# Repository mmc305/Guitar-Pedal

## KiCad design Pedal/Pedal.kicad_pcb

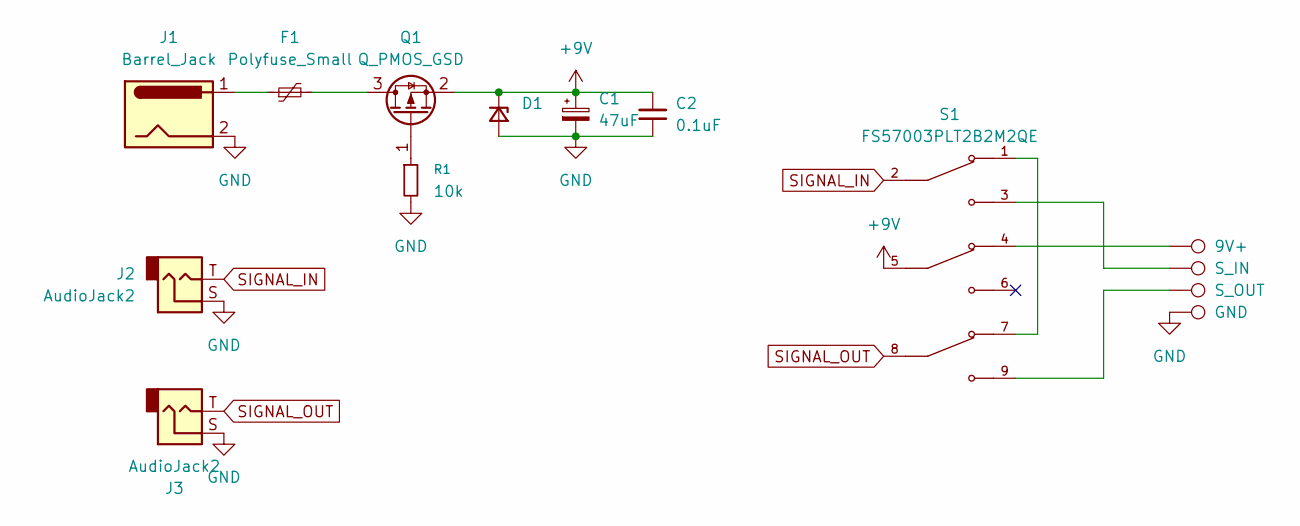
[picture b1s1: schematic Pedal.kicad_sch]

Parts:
C1: 47uF; CP_Radial_D6.3mm_P2.50mm
C2: 0.1uF; C_0603_1608Metric
D1: D_Zener_Small; D_SMA
F1: Polyfuse_Small; Fuse_2920_7451Metric
J1: Barrel_Jack; BarrelJack_GCT_DCJ200-10-A_Horizontal
J2, J3: AudioJack2; Jack_6.35mm_Neutrik_NMJ6HFD2_Horizontal
Q1: Q_PMOS_GSD; TSOT-23
R1: 10k; C_0603_1608Metric
S1: FS57003PLT2B2M2QE; SW_FS57003PLT2B2M2QE; PARTREV 4.2.2018
TP1: 9V+; TestPoint_Keystone_5019_Miniature
TP2: S_IN; TestPoint_Keystone_5019_Miniature
TP3: S_OUT; TestPoint_Keystone_5019_Miniature
TP4: GND; TestPoint_Keystone_5019_Miniature

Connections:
+9V: C1.1, C2.1, D1.1 (K), Q1.2 (S), S1.5
GND: C1.2, C2.2, D1.2 (A), J1.2, J2.S, J3.S, R1.2, TP4.1 (1_1)
unnamed: F1.1, J1.1
unnamed: F1.2, Q1.3 (D)
unnamed: Q1.1 (G), R1.1
unnamed: S1.1, S1.7
unnamed: S1.3, TP2.1 (1_1)
unnamed: S1.4, TP1.1 (1_1)
unnamed: S1.9, TP3.1 (1_1)
SIGNAL_IN: J2.T, S1.2
SIGNAL_OUT: J3.T, S1.8

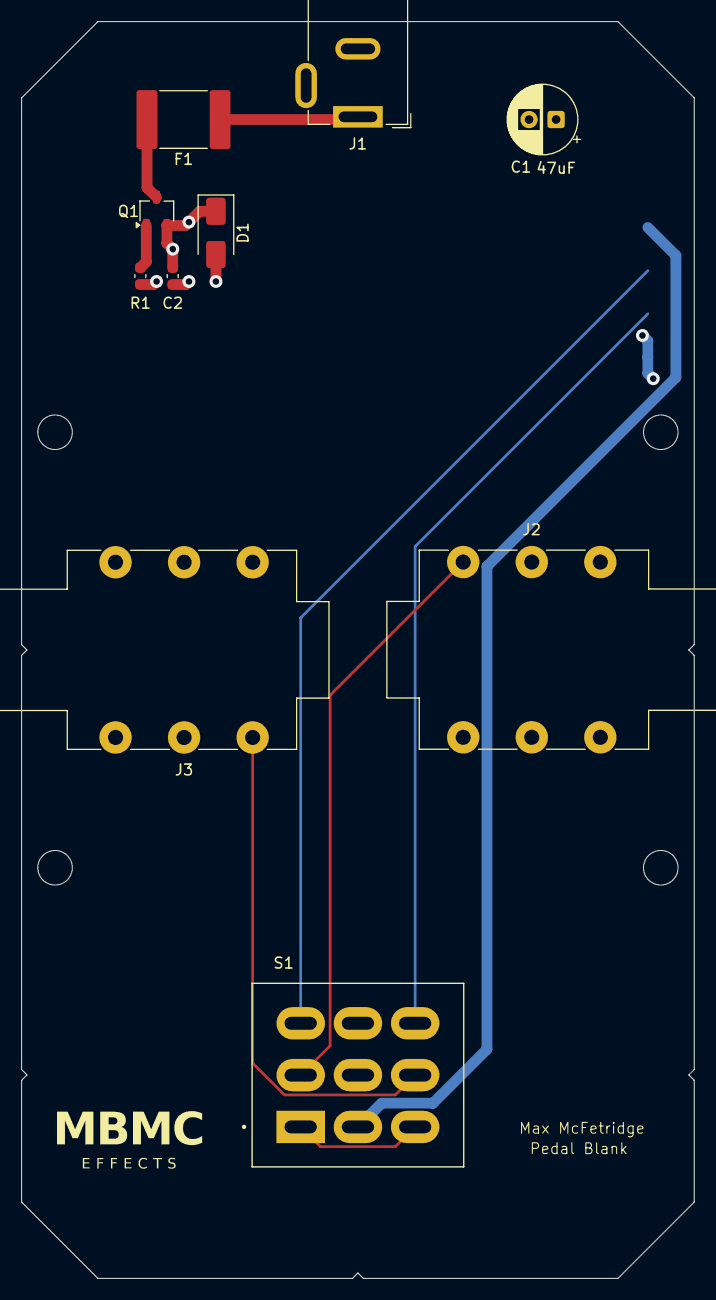
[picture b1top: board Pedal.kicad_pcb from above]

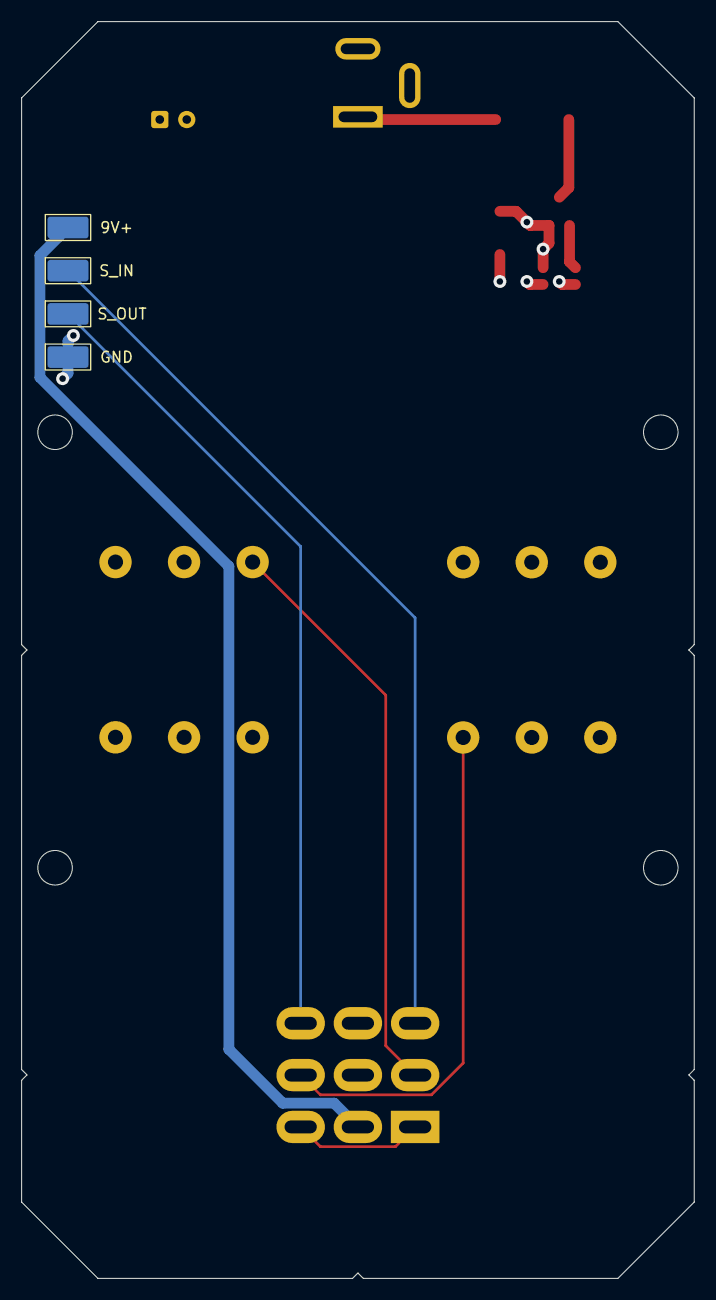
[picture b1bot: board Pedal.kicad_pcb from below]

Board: 4 copper layers, 62.3 x 116.4 mm, 14 parts (4 on the bottom side), 11 nets.

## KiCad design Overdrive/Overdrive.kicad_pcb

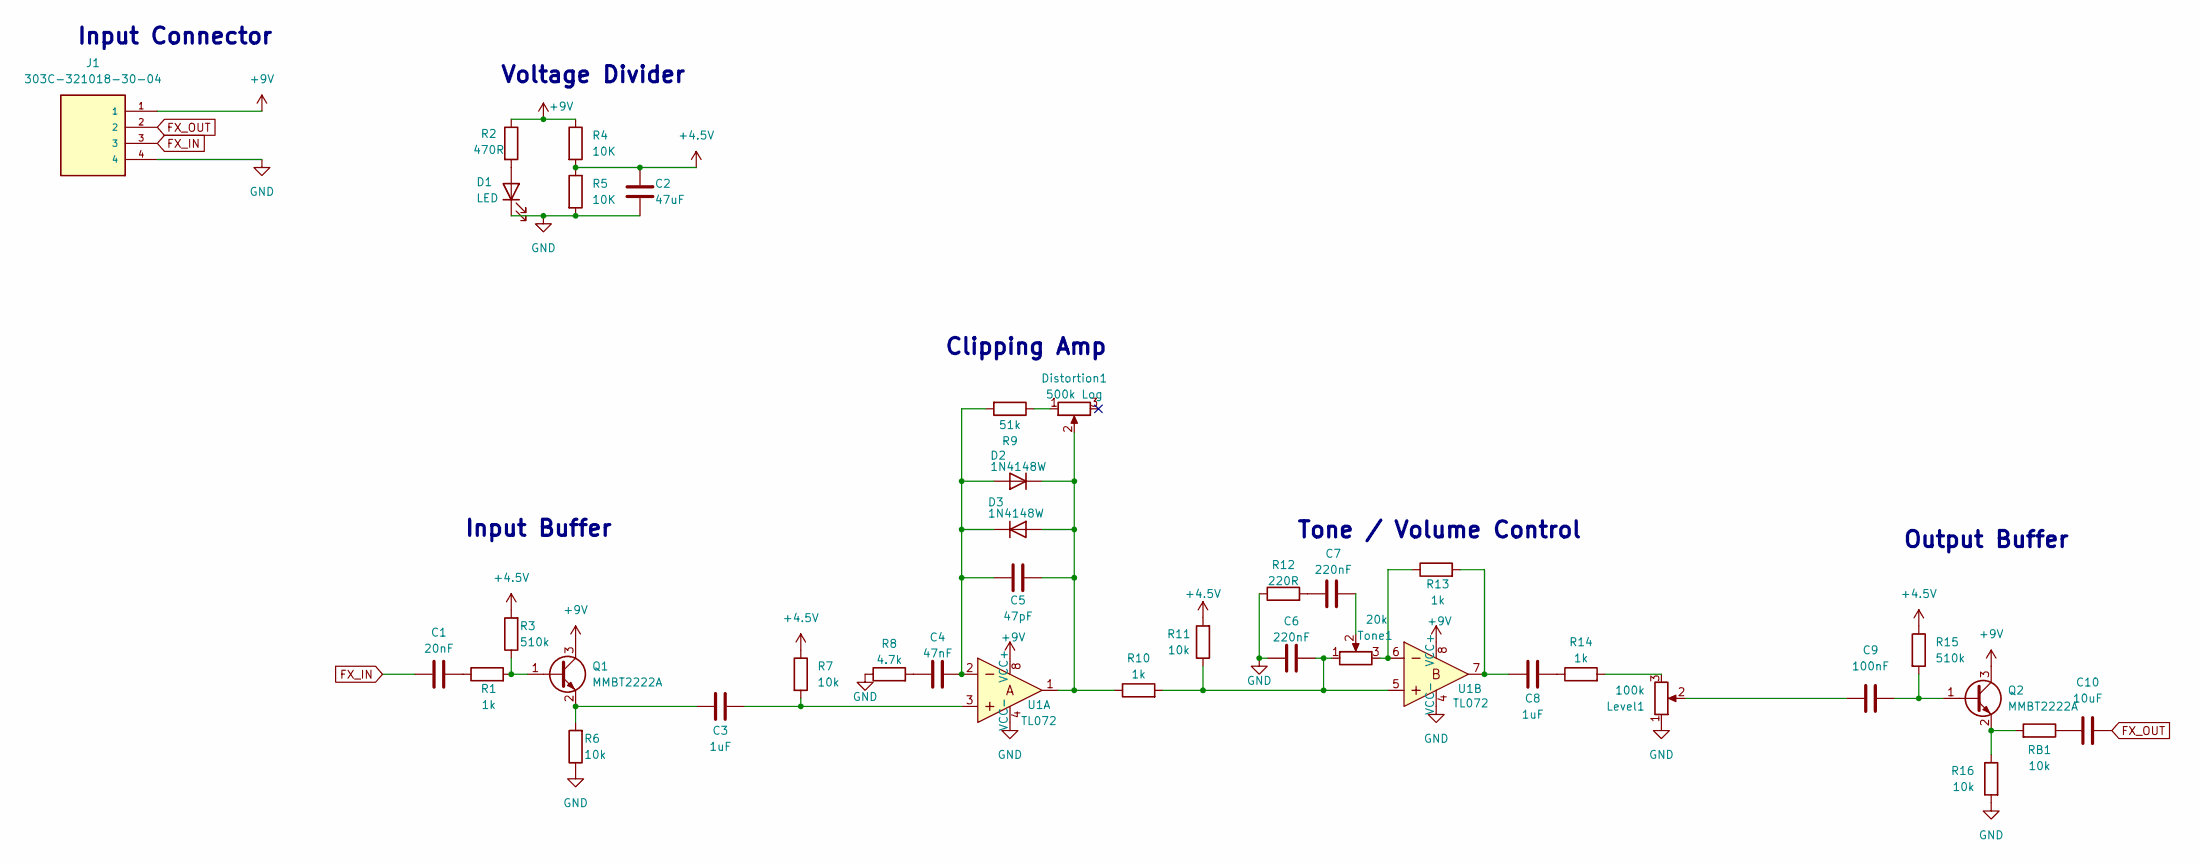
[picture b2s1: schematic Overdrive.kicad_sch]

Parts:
C1: 20nF; C_0603_1608Metric
C2: 47uF; C_0603_1608Metric
C3, C8: 1uF; C_0603_1608Metric
C4: 47nF; C_0603_1608Metric
C5: 47pF; C_0603_1608Metric
C6, C7: 220nF; C_0603_1608Metric
C9: 100nF; C_0603_1608Metric
C10: 10uF; C_0603_1608Metric
D1: LED; LED_D3.0mm_Clear
D2, D3: 1N4148W; D_SOD-123
Distortion1: 500k Log; POT_PTV09A-4020F_BRN
J1: 303C-321018-30-04; ATTEND_303C-321018-30-04; PARTREV 3; DigiKey_Part_Number 4827-303C-321018-30-04-ND
Level1: 100k; POT_PTV09A-4020F_BRN
Q1, Q2: MMBT2222A; SOT-23
R1, R10, R13, R14: 1k; R_0603_1608Metric
R2: 470R; R_0603_1608Metric
R3, R15: 510k; R_0603_1608Metric
R4, R5: 10K; R_0603_1608Metric
R6, R7, R11, R16: 10k; R_0603_1608Metric
R8: 4.7k; R_0603_1608Metric
R9: 51k; R_0603_1608Metric
R12: 220R; R_0603_1608Metric
RB1: 10k; R_0603_1608Metric
Tone1: 20k; POT_PTV09A-4020F_BRN
U1: TL072; SOIC-8_3.9x4.9mm_P1.27mm; MPN TL072CP; Digi-Key_PN 296-1775-5-ND

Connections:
+4.5V: C2.1, R3.2, R4.2, R5.1, R7.1, R11.2, R15.1
+9V: J1.1, Q1.3 (C), Q2.3 (C), R2.1, R4.1, U1.8 (VCC+)
FX_IN: C1.1, J1.3
FX_OUT: C10.2, J1.2
GND: C2.2, C6.1, D1.1 (K), J1.4, Level1.1, R5.2, R6.1, R8.1, R12.1, R16.2, U1.4 (VCC-)
unnamed: C1.2, R1.1
unnamed: C3.2, R7.2, U1.3
unnamed: C4.1, R8.2
unnamed: C6.2, R10.2, R11.1, Tone1.1, U1.5
unnamed: C7.1, Tone1.2
unnamed: C7.2, R12.2
unnamed: C8.1, R13.2, U1.7
unnamed: C8.2, R14.1
unnamed: C9.1, Level1.2
unnamed: C10.1, RB1.1
unnamed: D1.2 (A), R2.2
unnamed: C4.2, C5.1, D2.2 (A), D3.1 (K), R9.2, U1.2
unnamed: C5.2, D2.1 (K), D3.2 (A), Distortion1.2, R10.1, U1.1
unnamed: Distortion1.1, R9.1
unnamed: Level1.3, R14.2
unnamed: Q1.1 (B), R1.2, R3.1
unnamed: C3.1, Q1.2 (E), R6.2
unnamed: C9.2, Q2.1 (B), R15.2
unnamed: Q2.2 (E), R16.1, RB1.2
unnamed: R13.1, Tone1.3, U1.6

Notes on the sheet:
Input Buffer
Clipping Amp
Voltage Divider
Tone / Volume Control
Output Buffer
Input Connector

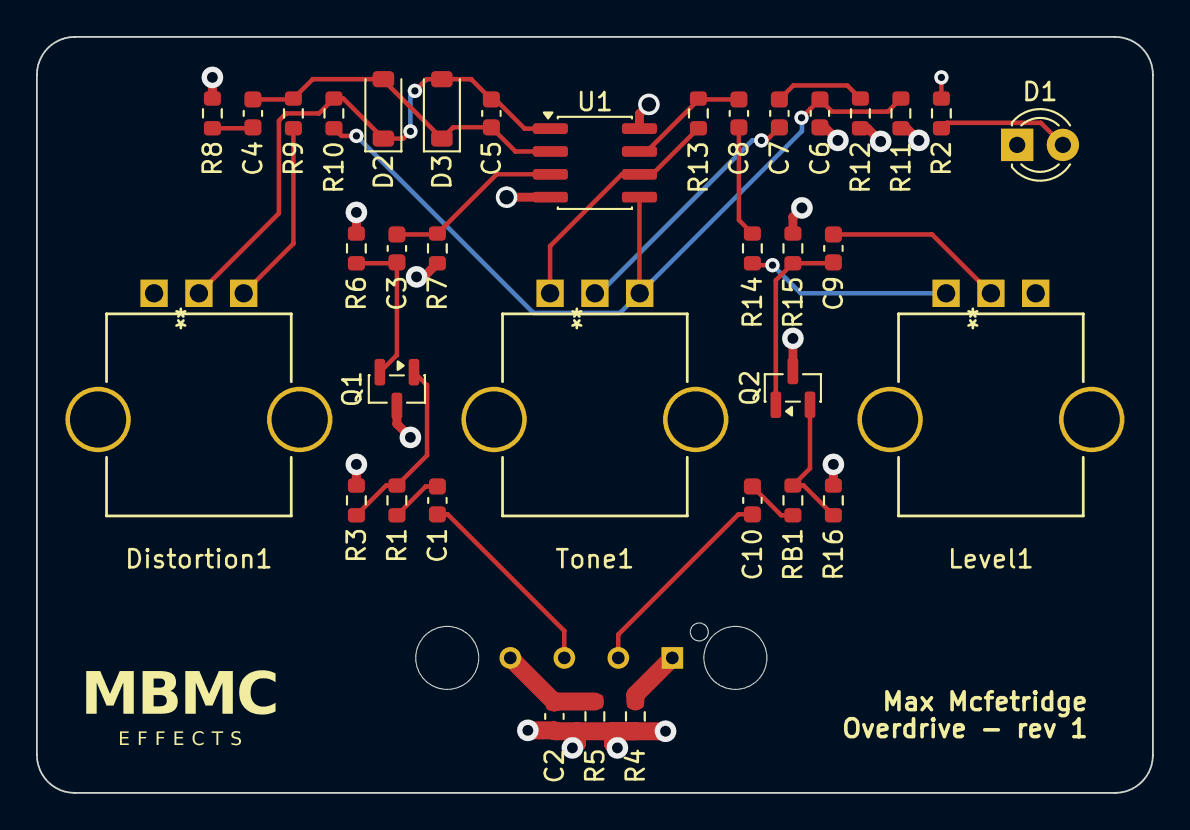
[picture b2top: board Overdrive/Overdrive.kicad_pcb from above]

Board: 4 copper layers, 62.0 x 42.0 mm, 37 parts (1 on the bottom side), 25 nets.

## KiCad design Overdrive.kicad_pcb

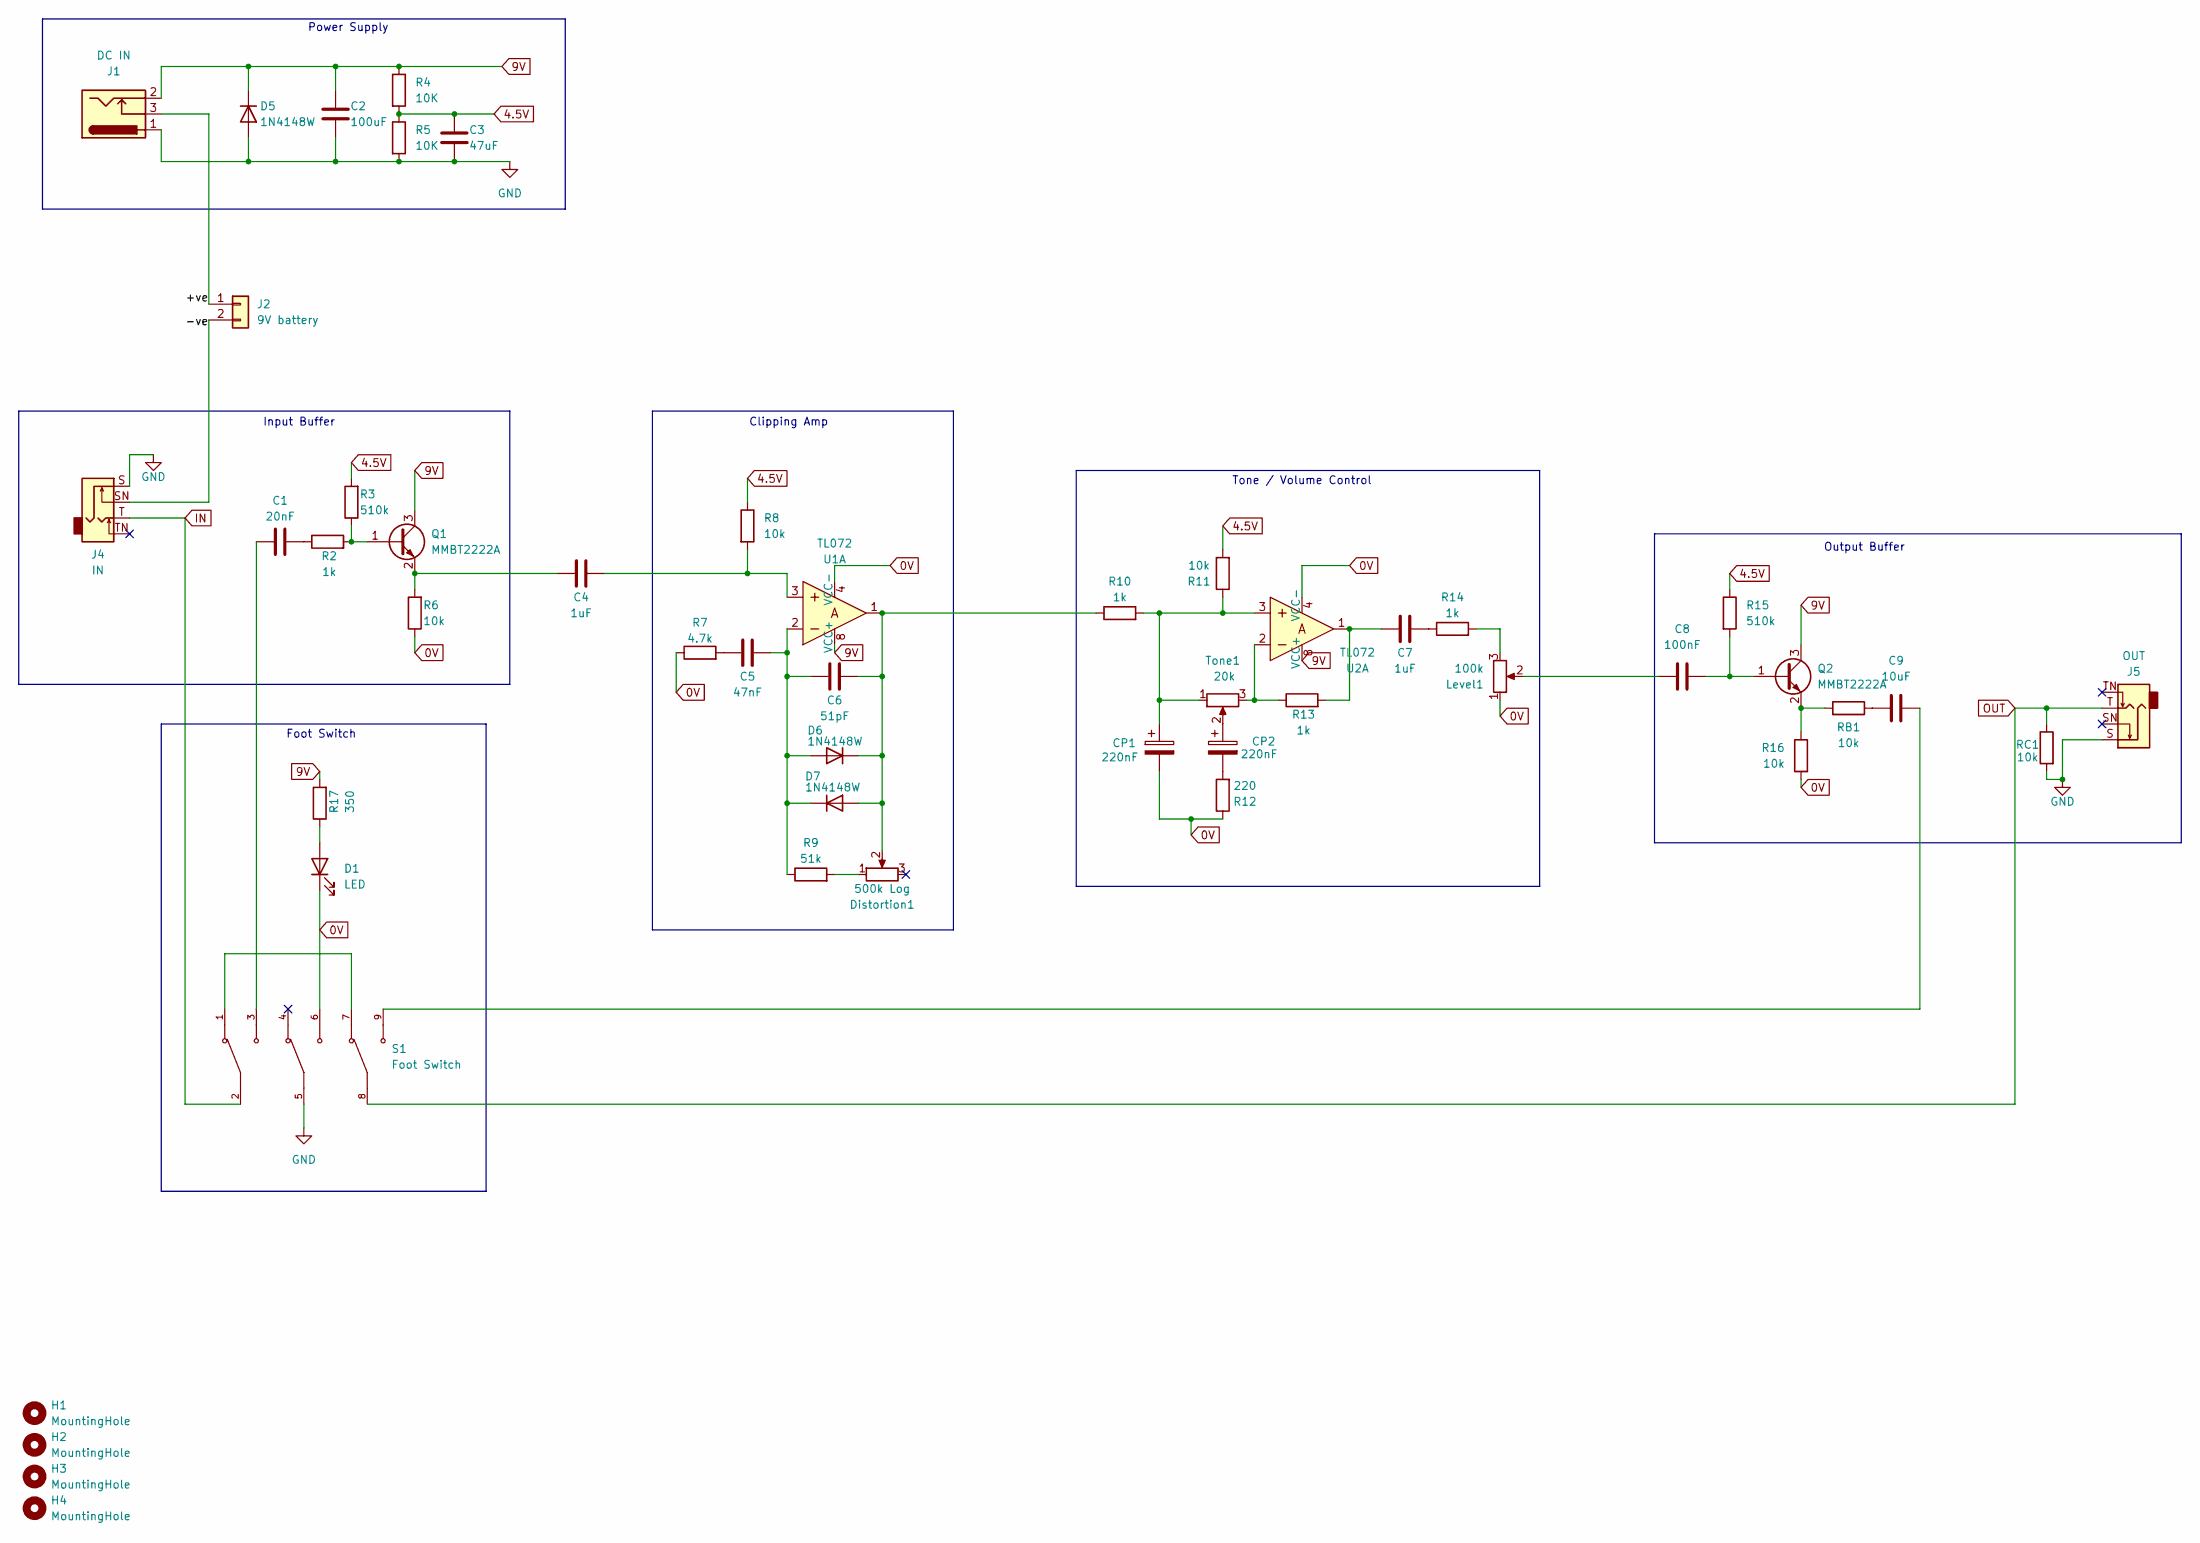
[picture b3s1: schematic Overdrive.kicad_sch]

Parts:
C1: 20nF; C_0603_1608Metric
C2: 100uF; C_1206_3216Metric
C3: 47uF; C_0805_2012Metric
C4, C7: 1uF; C_0603_1608Metric
C5: 47nF; C_0603_1608Metric
C6: 51pF; C_0603_1608Metric
C8: 100nF; C_0603_1608Metric
C9: 10uF; C_0603_1608Metric
CP1, CP2: 220nF; C_0603_1608Metric
D1: LED; LED_D3.0mm_Clear
D5, D6, D7: 1N4148W; D_SOD-123
Distortion1: 500k Log; Potentiometer_RK097_Single_Vertical
H1, H2, H3, H4: MountingHole; MountingHole_3.2mm_M3_Pad_Via
J1: DC IN; BarrelJack_GCT_DCJ200-10-A_Horizontal
J2: 9V battery; PinSocket_1x02_P2.00mm_Vertical
J4: IN; Jack_6.35mm_Neutrik_NMJ6HFD2_Horizontal
J5: OUT; Jack_6.35mm_Neutrik_NMJ6HFD2_Horizontal
Level1: 100k; Potentiometer_RK097_Single_Vertical
Q1, Q2: MMBT2222A; SOT-23
R2, R10, R13, R14: 1k; R_0603_1608Metric
R3, R15: 510k; R_0603_1608Metric
R4, R5: 10K; R_0603_1608Metric
R6, R8, R11, R16: 10k; R_0603_1608Metric
R7: 4.7k; R_0603_1608Metric
R9: 51k; R_0603_1608Metric
R12: 220; R_0603_1608Metric
R17: 350; R_0603_1608Metric
RB1: 10k; R_0603_1608Metric
RC1: 10k; R_0603_1608Metric
S1: Foot Switch; 3PDT Foot Switch
Tone1: 20k; Potentiometer_RK097_Single_Vertical
U1, U2: TL072; SOIC-8_3.9x4.9mm_P1.27mm; MPN TL072CP; Digi-Key_PN 296-1775-5-ND

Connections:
0V: CP1.2, D1.1 (K), Level1.1, R6.1, R7.1, R12.1, R16.2, S1.6, U1.4 (VCC-), U2.4 (VCC-)
4.5V: C3.1, R3.2, R4.2, R5.1, R8.1, R11.2, R15.1
9V: C2.1, D5.1 (K), J1.2, Q1.3 (C), Q2.3 (C), R4.1, R17.2, U1.8 (VCC+), U2.8 (VCC+)
/+ve: J1.3, J2.1
/-ve: J2.2, J4.SN
GND: C2.2, C3.2, D5.2 (A), J1.1, J4.S, J5.S, R5.2, RC1.2, S1.5
IN: J4.T, S1.2
unnamed: C1.1, S1.3
unnamed: C1.2, R2.1
unnamed: C4.2, R8.2, U1.3
unnamed: C5.1, R7.2
unnamed: C7.1, R13.2, U2.1
unnamed: C7.2, R14.1
unnamed: C8.1, Level1.2
unnamed: C9.1, RB1.1
unnamed: C9.2, S1.9
unnamed: CP1.1, R10.2, R11.1, Tone1.1, U2.3
unnamed: CP2.1, Tone1.2
unnamed: CP2.2, R12.2
unnamed: D1.2 (A), R17.1
unnamed: C5.2, C6.1, D6.2 (A), D7.1 (K), R9.1, U1.2
unnamed: C6.2, D6.1 (K), D7.2 (A), Distortion1.2, R10.1, U1.1
unnamed: Distortion1.1, R9.2
unnamed: Level1.3, R14.2
unnamed: Q1.1 (B), R2.2, R3.1
unnamed: C4.1, Q1.2 (E), R6.2
unnamed: C8.2, Q2.1 (B), R15.2
unnamed: Q2.2 (E), R16.1, RB1.2
unnamed: R13.1, Tone1.3, U2.2
unnamed: S1.1, S1.7
OUT: J5.T, RC1.1, S1.8

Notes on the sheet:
Clipping Amp
Output Buffer
Tone / Volume Control
Input Buffer
Foot Switch
Power Supply

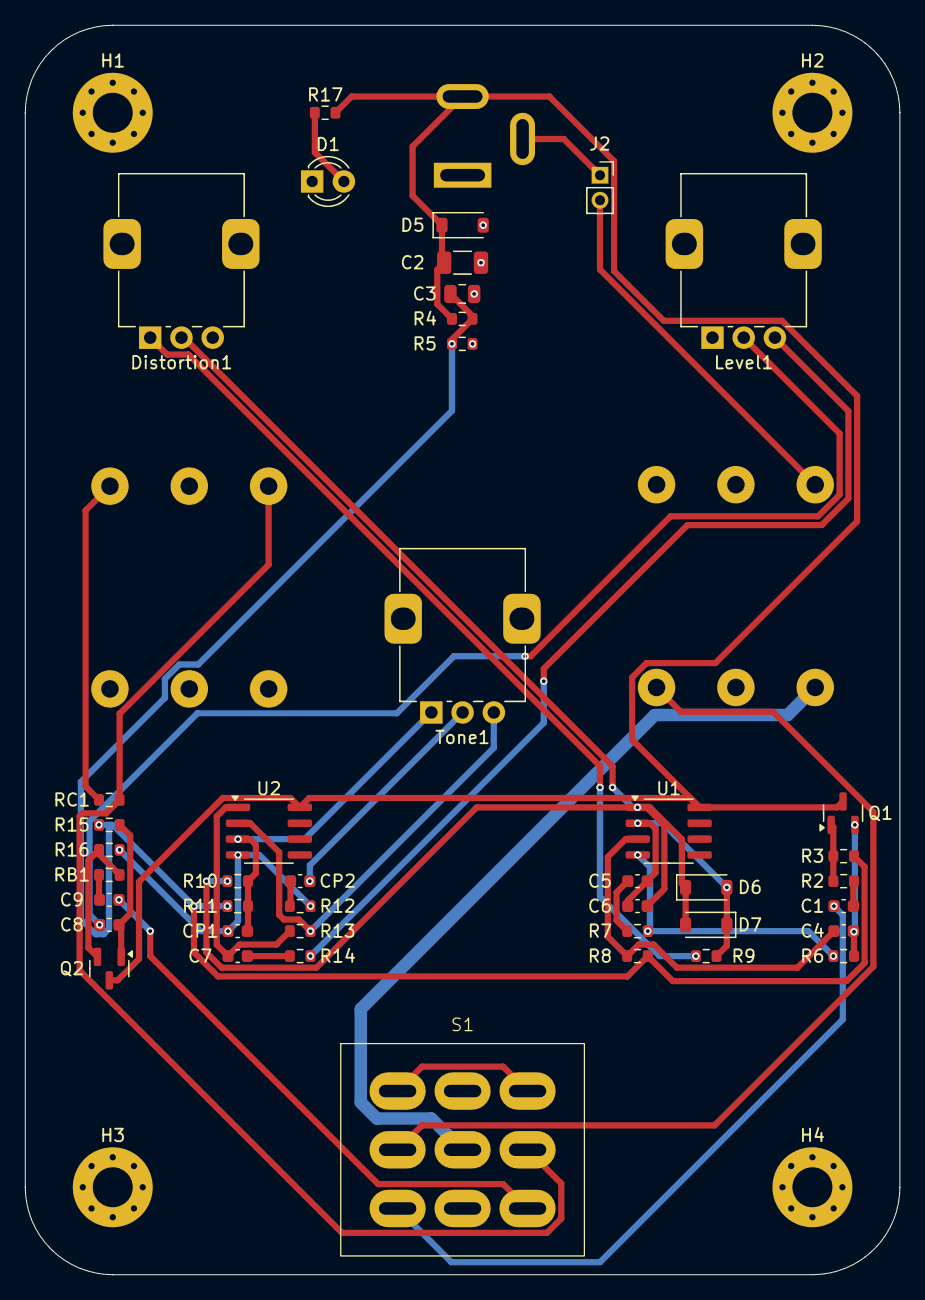
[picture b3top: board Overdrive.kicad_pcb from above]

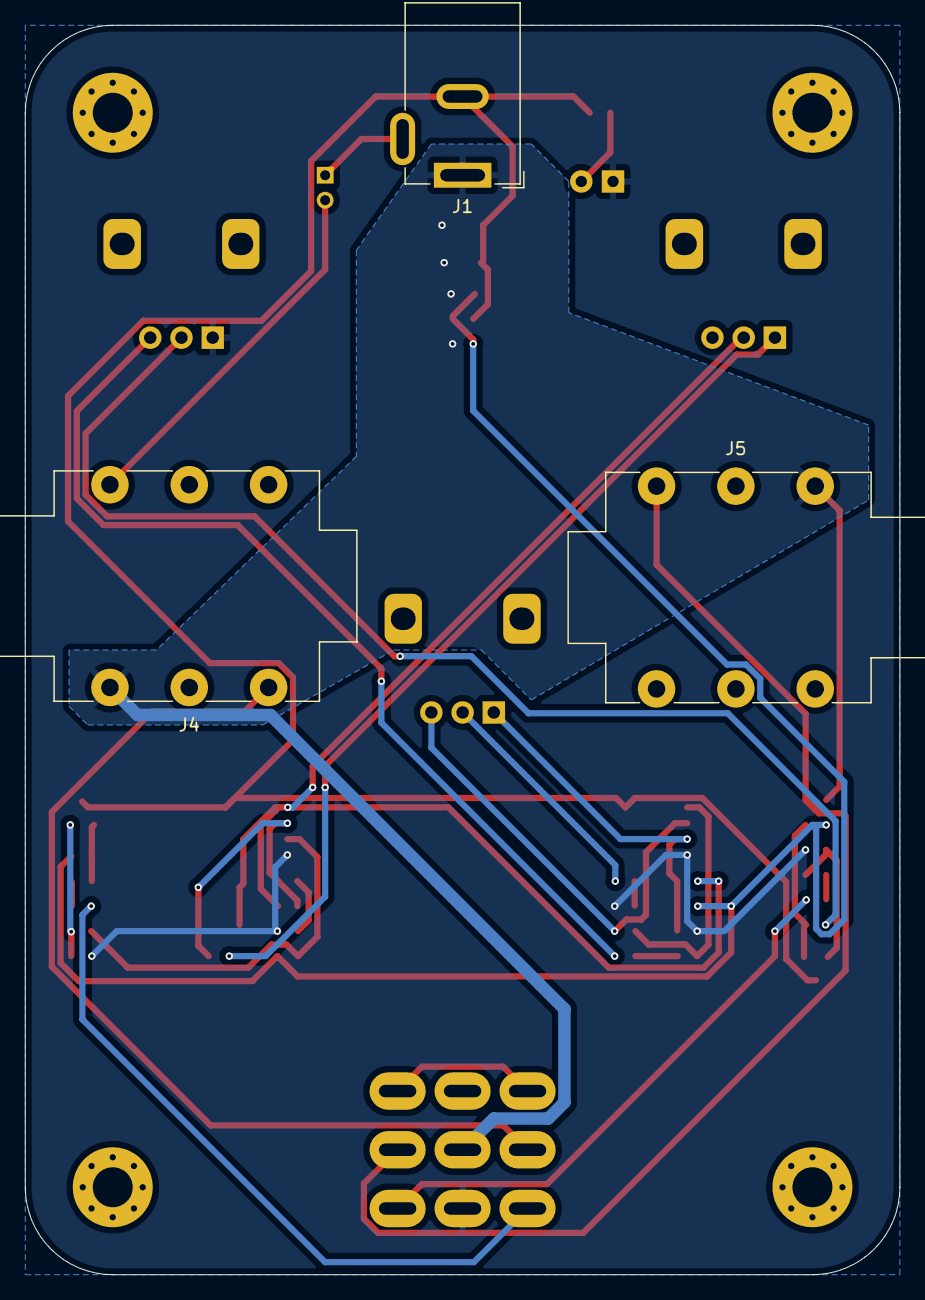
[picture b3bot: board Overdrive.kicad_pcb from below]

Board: 2 copper layers, 70.0 x 100.0 mm, 49 parts (3 on the bottom side), 31 nets.

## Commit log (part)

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2025-06-23 updated schematic and PCB layout, 70 x 100 size, updated footprints of footswitch, Barrel Conn, audio jacks, LED and Pots, 9v Battery Compatable, corrected pot polarity, Power is cut at switch, No mo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
2025-06-29 renamed project to 'Overdrive' and cleaned up unused files
2025-06-29 re oorganised folders
2025-06-29 re organised folders
2025-07-03 last commit before changing PCB layout to match Delay Pedal shape (110mmx60mm).
2025-07-03 Redesigned PCB layout to be 110mm x 60mm
2025-07-24 added hard clipping switch, changed electrolytic caps to be THT and to be sources separately.
